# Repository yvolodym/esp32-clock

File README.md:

# esp32-clock

This project is intended as training for esp8266. The aim of this project is to develop a low-energy clock, developed in C by [espressif](https://www.espressif.com/) with associated PCB in [KiCad](https://www.kicad.org/).

### URI
* https://docs.lvgl.io/master/intro/introduction.html
* https://github.com/espressif/esp-bsp/tree/master/components/lcd/esp_lcd_gc9a01
* https://github.com/espressif/esp-bsp
* https://github.com/lvgl/lv_port_esp32
* https://github.com/lvgl/lvgl_esp32_drivers/blob/master/README.md

### HARDWARE
ESP32-PICO-V3
CR2032

### Software
* https://github.com/espressif/esp-idf/blob/master/examples/peripherals/lcd/spi_lcd_touch/README.md
-------------------------------
* https://github.com/espressif/esp-idf/tree/v5.4/examples/peripherals/lcd/i2c_oled/main
* https://github.com/UsefulElectronics/esp32s3-gc9a01-lvgl/blob/main/main/Kconfig.projbuild
* https://github.com/liyanboy74/gc9a01-esp-idf
* https://github.com/somebox/esp32-GC9A01-round/blob/main/src/main.cpp

### Schematik
* https://embeddedprojects101.com/design-a-battery-powered-stm32-board-with-usb/

### JLCPCB
* https://jlcpcb.com/parts/componentSearch

### Video
* https://www.youtube.com/watch?v=S_p0YV-JlfU

### WIFI Provisioning
* https://docs.espressif.com/projects/esp-idf/en/stable/esp32/api-reference/provisioning/wifi_provisioning.html#
* https://github.com/espressif/esp-idf/blob/master/examples/provisioning/wifi_prov_mgr/README.md

| Pin | Name |
|-----|------|
|IO19 |RST   |
|IO10 |SCL   |
|IO20 |CS    |
|IO21 |DC    |
|IO22 |MOSI  |

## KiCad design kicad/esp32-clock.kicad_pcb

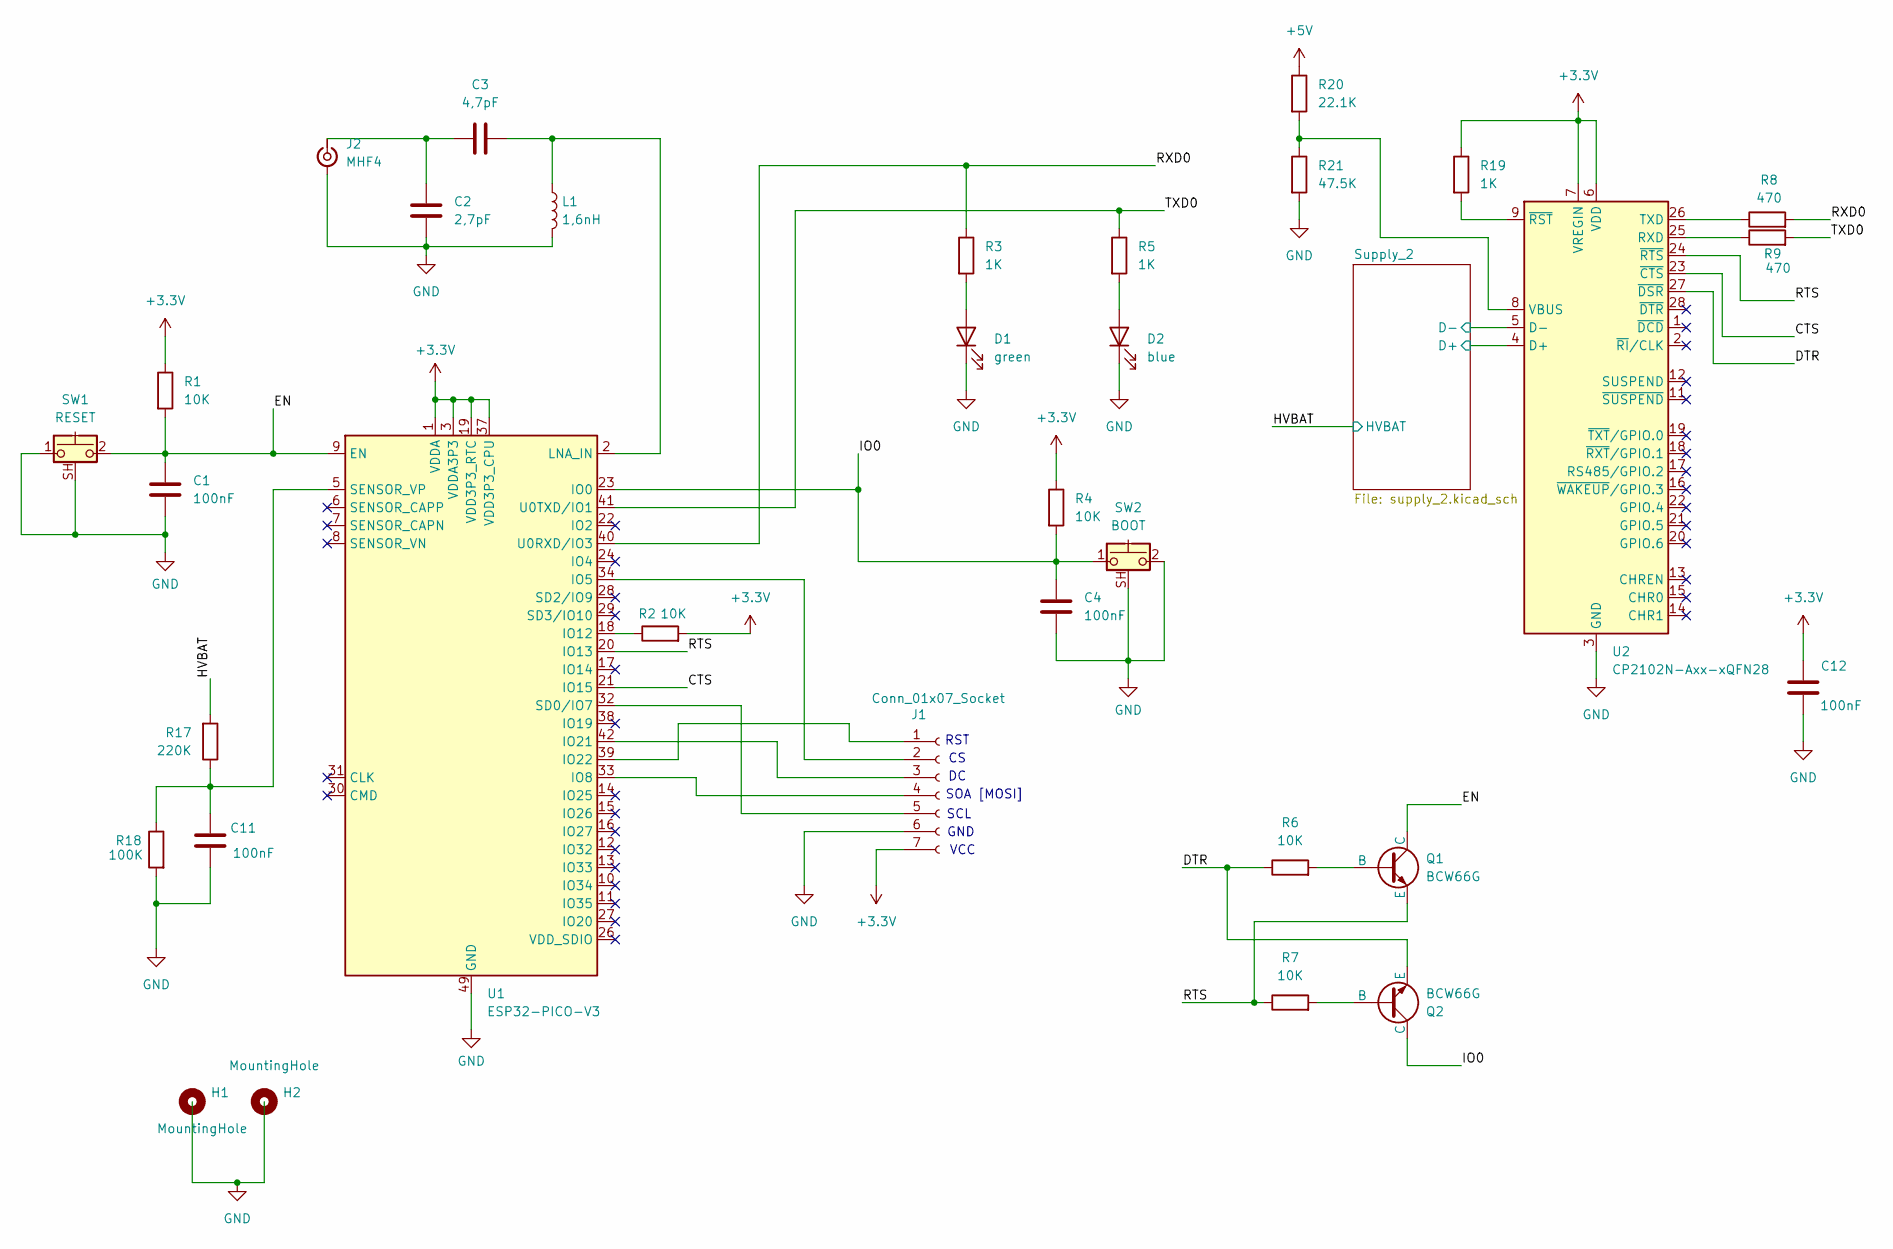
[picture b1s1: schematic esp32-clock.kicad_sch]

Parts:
C1, C4, C11, C12: 100nF; C_0805_2012Metric
C2: 2,7pF; C_0805_2012Metric
C3: 4,7pF; C_0805_2012Metric
D1: green; D_0805_2012Metric
D2: blue; D_0805_2012Metric
H1, H2: MountingHole; MountingHole_2.2mm_M2_DIN965_Pad
J1: Conn_01x07_Socket; PinSocket_1x07_P2.54mm_Vertical
J2: MHF4
L1: 1,6nH; D_0805_2012Metric
Q1, Q2: BCW66G; SOT-23
R1, R2, R4: 10K; R_0805_2012Metric
R3, R5, R19: 1K; R_0805_2012Metric
R6, R7: 10K; R_0805_2012Metric; LCSC C25819
R8, R9: 470; R_0805_2012Metric; LCSC C25819
R17: 220K; R_0805_2012Metric
R18: 100K; R_0805_2012Metric
R20: 22.1K; R_0805_2012Metric
R21: 47.5K; R_0805_2012Metric
SW1: RESET; SW_Push_1P1T_NO_CK_KMR2
SW2: BOOT; SW_Push_1P1T_NO_CK_KMR2
U1: ESP32-PICO-V3; QFN-48-1EP_7x7mm_P0.5mm_EP5.3x5.3mm
U2: CP2102N-Axx-xQFN28; QFN-28-1EP_5x5mm_P0.5mm_EP3.35x3.35mm

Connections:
+3.3V: C12.1, J1.7, R1.1, R2.2, R4.1, R19.1, U1.1 (VDDA), U1.3 (VDDA3P3), U1.4 (VDDA3P3), U1.19 (VDD3P3_RTC), U1.37 (VDD3P3_CPU), U1.43 (VDDA), U1.46 (VDDA), U2.6 (VDD), U2.7 (VREGIN); also elsewhere on the board
+5V: R20.1; also elsewhere on the board
/CTS: U1.21 (IO15), U2.23 (~CTS)
/DTR: Q2.3 (E), R6.1, U2.27 (~DSR)
/EN: C1.1, Q1.1 (C), R1.2, SW1.2, U1.9 (EN)
/HVBAT: R17.2; also elsewhere on the board
/IO0: C4.1, Q2.1 (C), R4.2, SW2.1, U1.23 (IO0)
/RTS: Q1.3 (E), R7.1, U1.20 (IO13), U2.24 (~RTS)
/RXD0: R3.1, R8.2, U1.40 (U0RXD/IO3)
/Supply_2/D+: U2.4 (D+); also elsewhere on the board
/Supply_2/D-: U2.5 (D-); also elsewhere on the board
/TXD0: R5.1, R9.2, U1.41 (U0TXD/IO1)
GND: C1.2, C2.2, C4.2, C11.2, C12.2, D1.1 (K), D2.1 (K), J1.6, J2.2 (GND), L1.2, R18.2, R21.2, SW1.1, SW1.SH (B), SW2.2, SW2.SH (B), U1.49 (GND), U2.3 (GND), U2.29 (GND); also elsewhere on the board
unnamed: D1.2 (A), R3.2
unnamed: D2.2 (A), R5.2
unnamed: J1.1, U1.39 (IO22)
unnamed: J1.2, U1.34 (IO5)
unnamed: J1.3, U1.42 (IO21)
unnamed: J1.4, U1.33 (IO8)
unnamed: J1.5, U1.32 (SD0/IO7)
unnamed: C2.1, C3.1, J2.1 (SIGNAL)
unnamed: Q1.2 (B), R6.2
unnamed: Q2.2 (B), R7.2
unnamed: R2.1, U1.18 (IO12)
unnamed: C3.2, L1.1, U1.2 (LNA_IN)
unnamed: C11.1, R17.1, R18.1, U1.5 (SENSOR_VP)
unnamed: R9.1, U2.25 (RXD)
unnamed: R8.1, U2.26 (TXD)
unnamed: R20.2, R21.1, U2.8 (VBUS)
unnamed: R19.2, U2.9 (~RST)

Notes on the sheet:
RST
SCL
VCC
GND
SOA [MOSI]

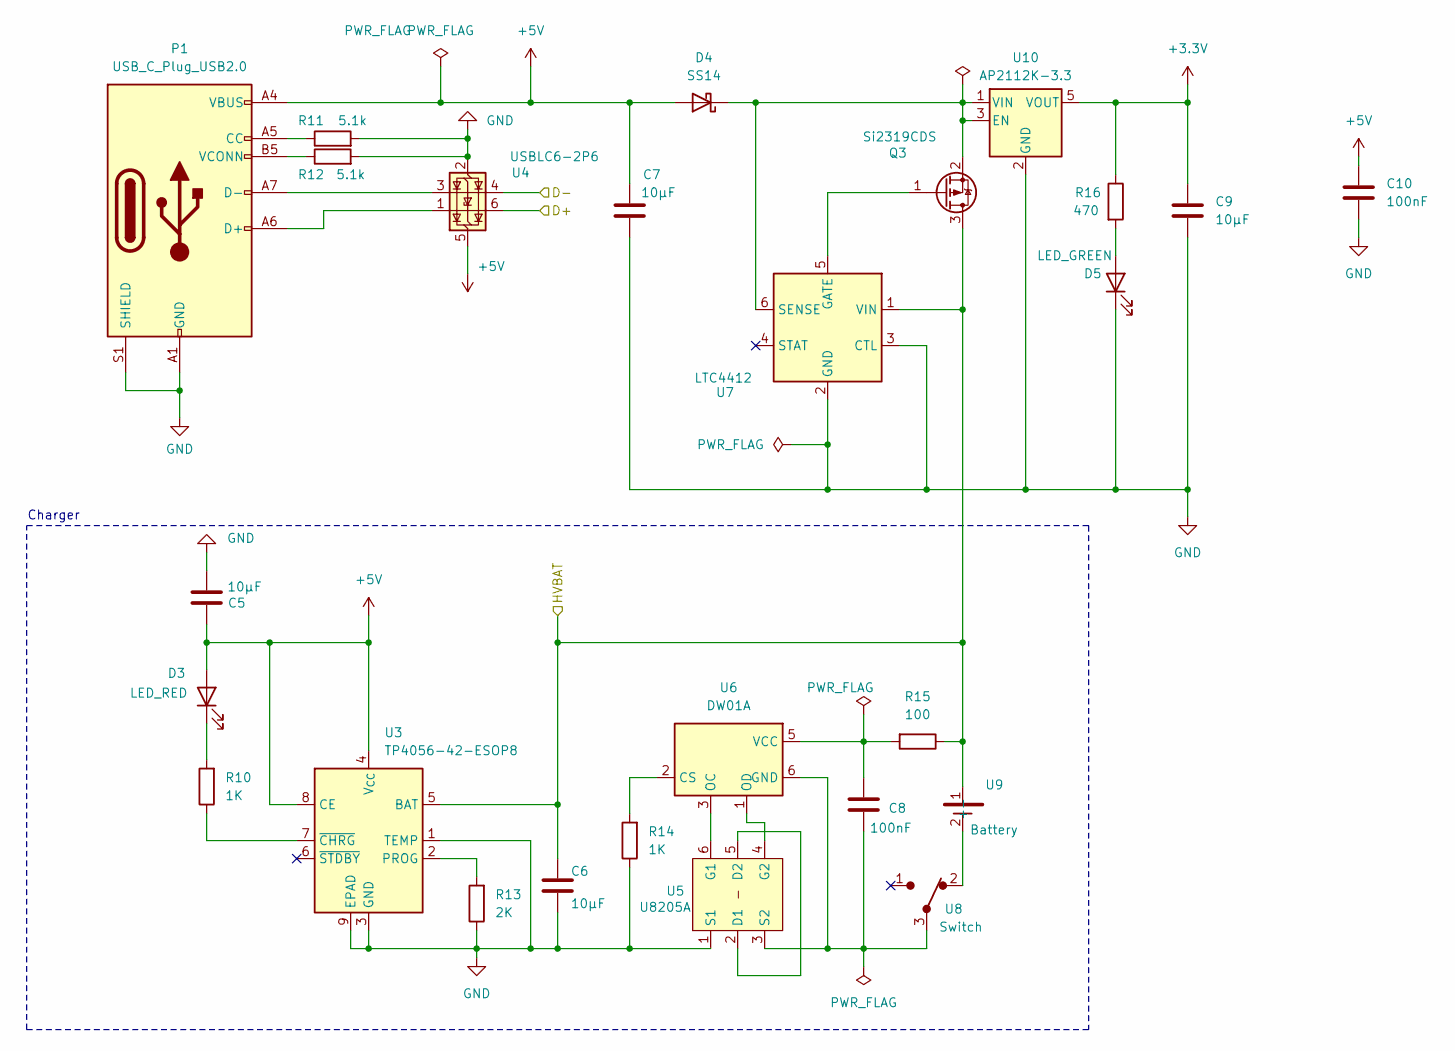
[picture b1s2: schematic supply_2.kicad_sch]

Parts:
C5, C6, C7, C9: 10µF; C_0805_2012Metric
C8, C10: 100nF; C_0805_2012Metric
D3: LED_RED; D_0805_2012Metric
D4: SS14; D_SMA
D5: LED_GREEN; D_0805_2012Metric
P1: USB_C_Plug_USB2.0; USB_C_Receptacle_GCT_USB4105-xx-A_16P_TopMnt_Horizontal; LCSC C456012
Q3: Si2319CDS; SOT-23
R10, R14: 1K; R_0805_2012Metric
R11, R12: 5.1k; R_0805_2012Metric
R13: 2K; R_0805_2012Metric
R15: 100; R_0805_2012Metric
R16: 470; R_0805_2012Metric
U3: TP4056-42-ESOP8; SOIC-8-1EP_3.9x4.9mm_P1.27mm_EP2.41x3.3mm_ThermalVias
U4: USBLC6-2P6; SOT-23-6
U5: U8205A; SOT-23-6
U6: DW01A; SOT-23-6
U7: LTC4412; TSOT-23-6
U8: Switch; SW_SPDT_PCM12
U9: Battery; CR2032
U10: AP2112K-3.3; SOT-23-5

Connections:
+3.3V: C9.1, R16.1, U10.5 (VOUT); also elsewhere on the board
+5V: C5.1, C7.1, C10.2, D3.2 (A), D4.2 (A), P1.A4 (VBUS), P1.A9 (VBUS), P1.B4 (VBUS), P1.B9 (VBUS), U3.4 (V_{CC}), U3.8 (CE), U4.5 (VBUS); also elsewhere on the board
/HVBAT: C6.1, Q3.3 (D), R15.1, U3.5 (BAT), U7.1 (VIN), U9.1 (+); also elsewhere on the board
/Supply_2/D+: U4.6 (I/O1); also elsewhere on the board
/Supply_2/D-: U4.4 (I/O2); also elsewhere on the board
GND: C5.2, C6.2, C7.2, C9.2, C10.1, D5.1 (K), P1.A1 (GND), P1.A12 (GND), P1.B1 (GND), P1.B12 (GND), P1.S1 (SHIELD), R11.2, R12.2, R13.1, R14.1, U3.1 (TEMP), U3.3 (GND), U3.9 (EPAD), U4.2 (GND), U5.1 (S1), U7.2 (GND), U7.3 (CTL), U10.2 (GND); also elsewhere on the board
unnamed: D3.1 (K), R10.2
unnamed: D4.1 (K), Q3.2 (S), U7.6 (SENSE), U10.1 (VIN), U10.3 (EN)
unnamed: D5.2 (A), R16.2
unnamed: P1.A5 (CC), R11.1
unnamed: P1.A6 (D+), U4.1 (I/O1)
unnamed: P1.A7 (D-), U4.3 (I/O2)
unnamed: P1.B5 (VCONN), R12.1
unnamed: Q3.1 (G), U7.5 (GATE)
unnamed: R13.2, U3.2 (PROG)
unnamed: R10.1, U3.7 (~CHRG)
unnamed: U5.2 (D1), U5.5 (D2)
unnamed: U5.6 (G1), U6.3 (OC)
unnamed: U5.4 (G2), U6.1 (OD)
unnamed: C8.1, U5.3 (S2), U6.6 (GND), U8.3
unnamed: R14.2, U6.2 (CS)
unnamed: C8.2, R15.2, U6.5 (VCC)
unnamed: U8.2, U9.2 (-)

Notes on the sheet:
Charger

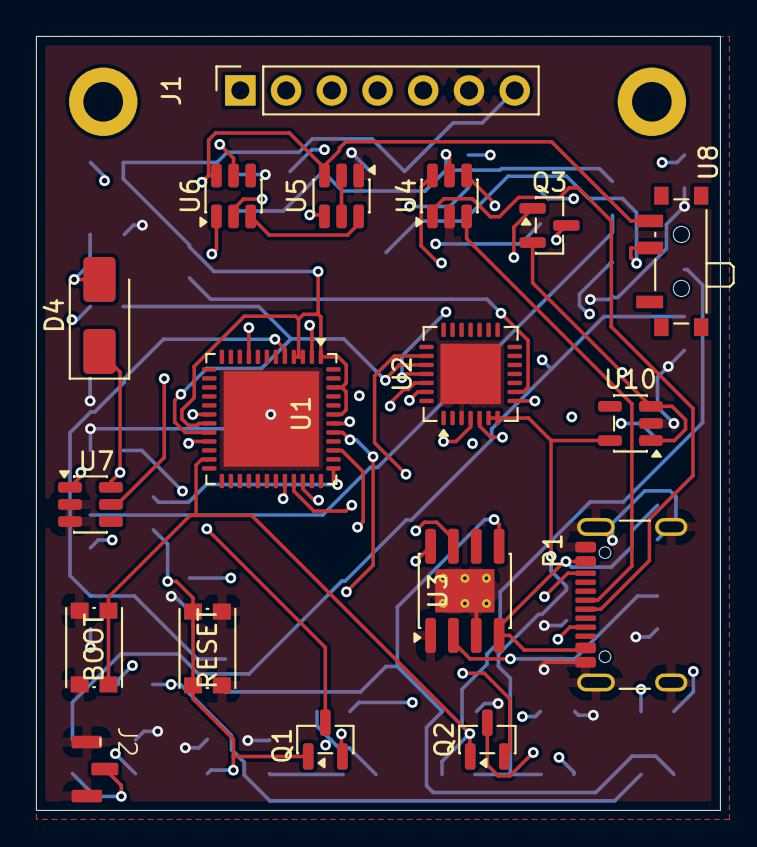
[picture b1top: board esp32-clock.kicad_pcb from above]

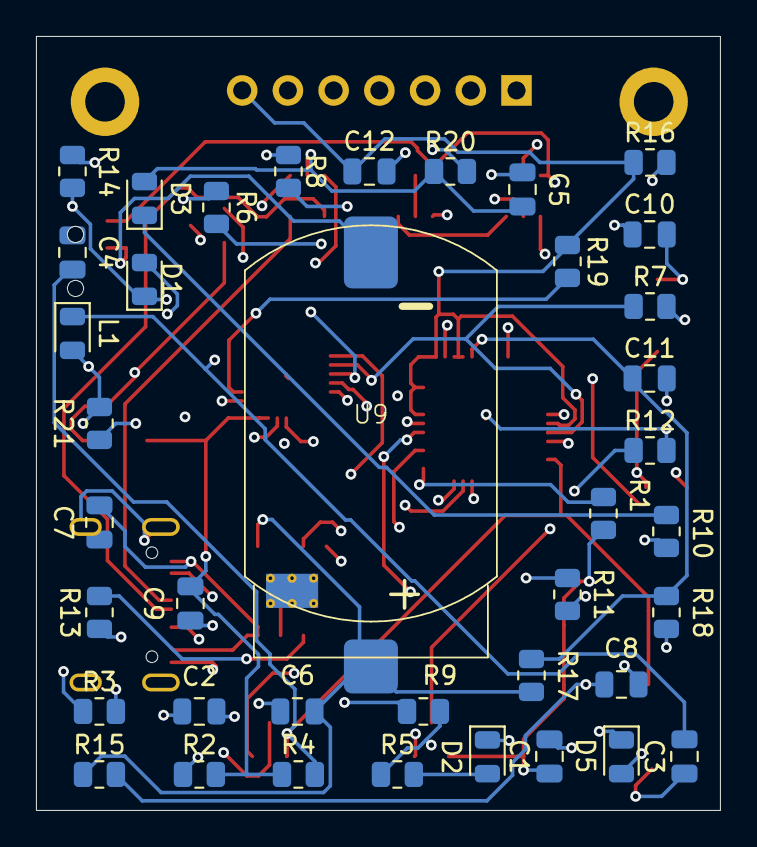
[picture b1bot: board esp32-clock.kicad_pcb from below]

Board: 4 copper layers, 38.0 x 43.0 mm, 59 parts (39 on the bottom side), 47 nets.

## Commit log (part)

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2024-11-26 init
2025-02-24 sharded for all version
2025-03-01 EUGEN
